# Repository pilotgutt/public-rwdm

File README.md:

# Real-Time Monitoring of Diver Status using Wireless Subsea Transmission (RWDM)

Real-Time Monitoring of Diver Status using Wireless Subsea Transmission (RWDM) is a bachelor project aimed at monitoring diver status in real time and communicating information through a wireless subsea transmission link.
This bachelor project marks the culmination of our studies in the TS3000 program at the Department of Microsystems, Faculty of Technology, Natural Sciences and Maritime Sciences. The work was carried out during the spring semester of 2026 and represents a collaborative research and development effort focused on Real-Time Wireless Diver Monitoring (RWDM).

## Repository overview

This repository contains components implemented in multiple languages:

- **C++ (56.3%)** — core/system components and performance-critical logic
- **TypeScript (17.8%)** — application/UI and supporting tooling
- **Python (15.6%)** — analysis, scripting, prototyping, or supporting services
- **C (2.3%)** — low-level/embedded or interoperability components
- **HTML (3.5%) / CSS (4.5%)** — web UI assets

## What this project is for

Typical goals for a system like this include:

- Collecting diver telemetry/status signals
- Transmitting data over a subsea wireless link
- Displaying/monitoring status in (near) real time
- Logging data for later review and analysis

## Contributing

Contributions are welcome.

Suggested workflow:

1. Fork the repo (or create a branch if you have access)
2. Make changes with clear commit messages
3. Add/update documentation and tests where applicable
4. Open a pull request with a concise description and reproduction steps (if relevant)

## License

MIT License

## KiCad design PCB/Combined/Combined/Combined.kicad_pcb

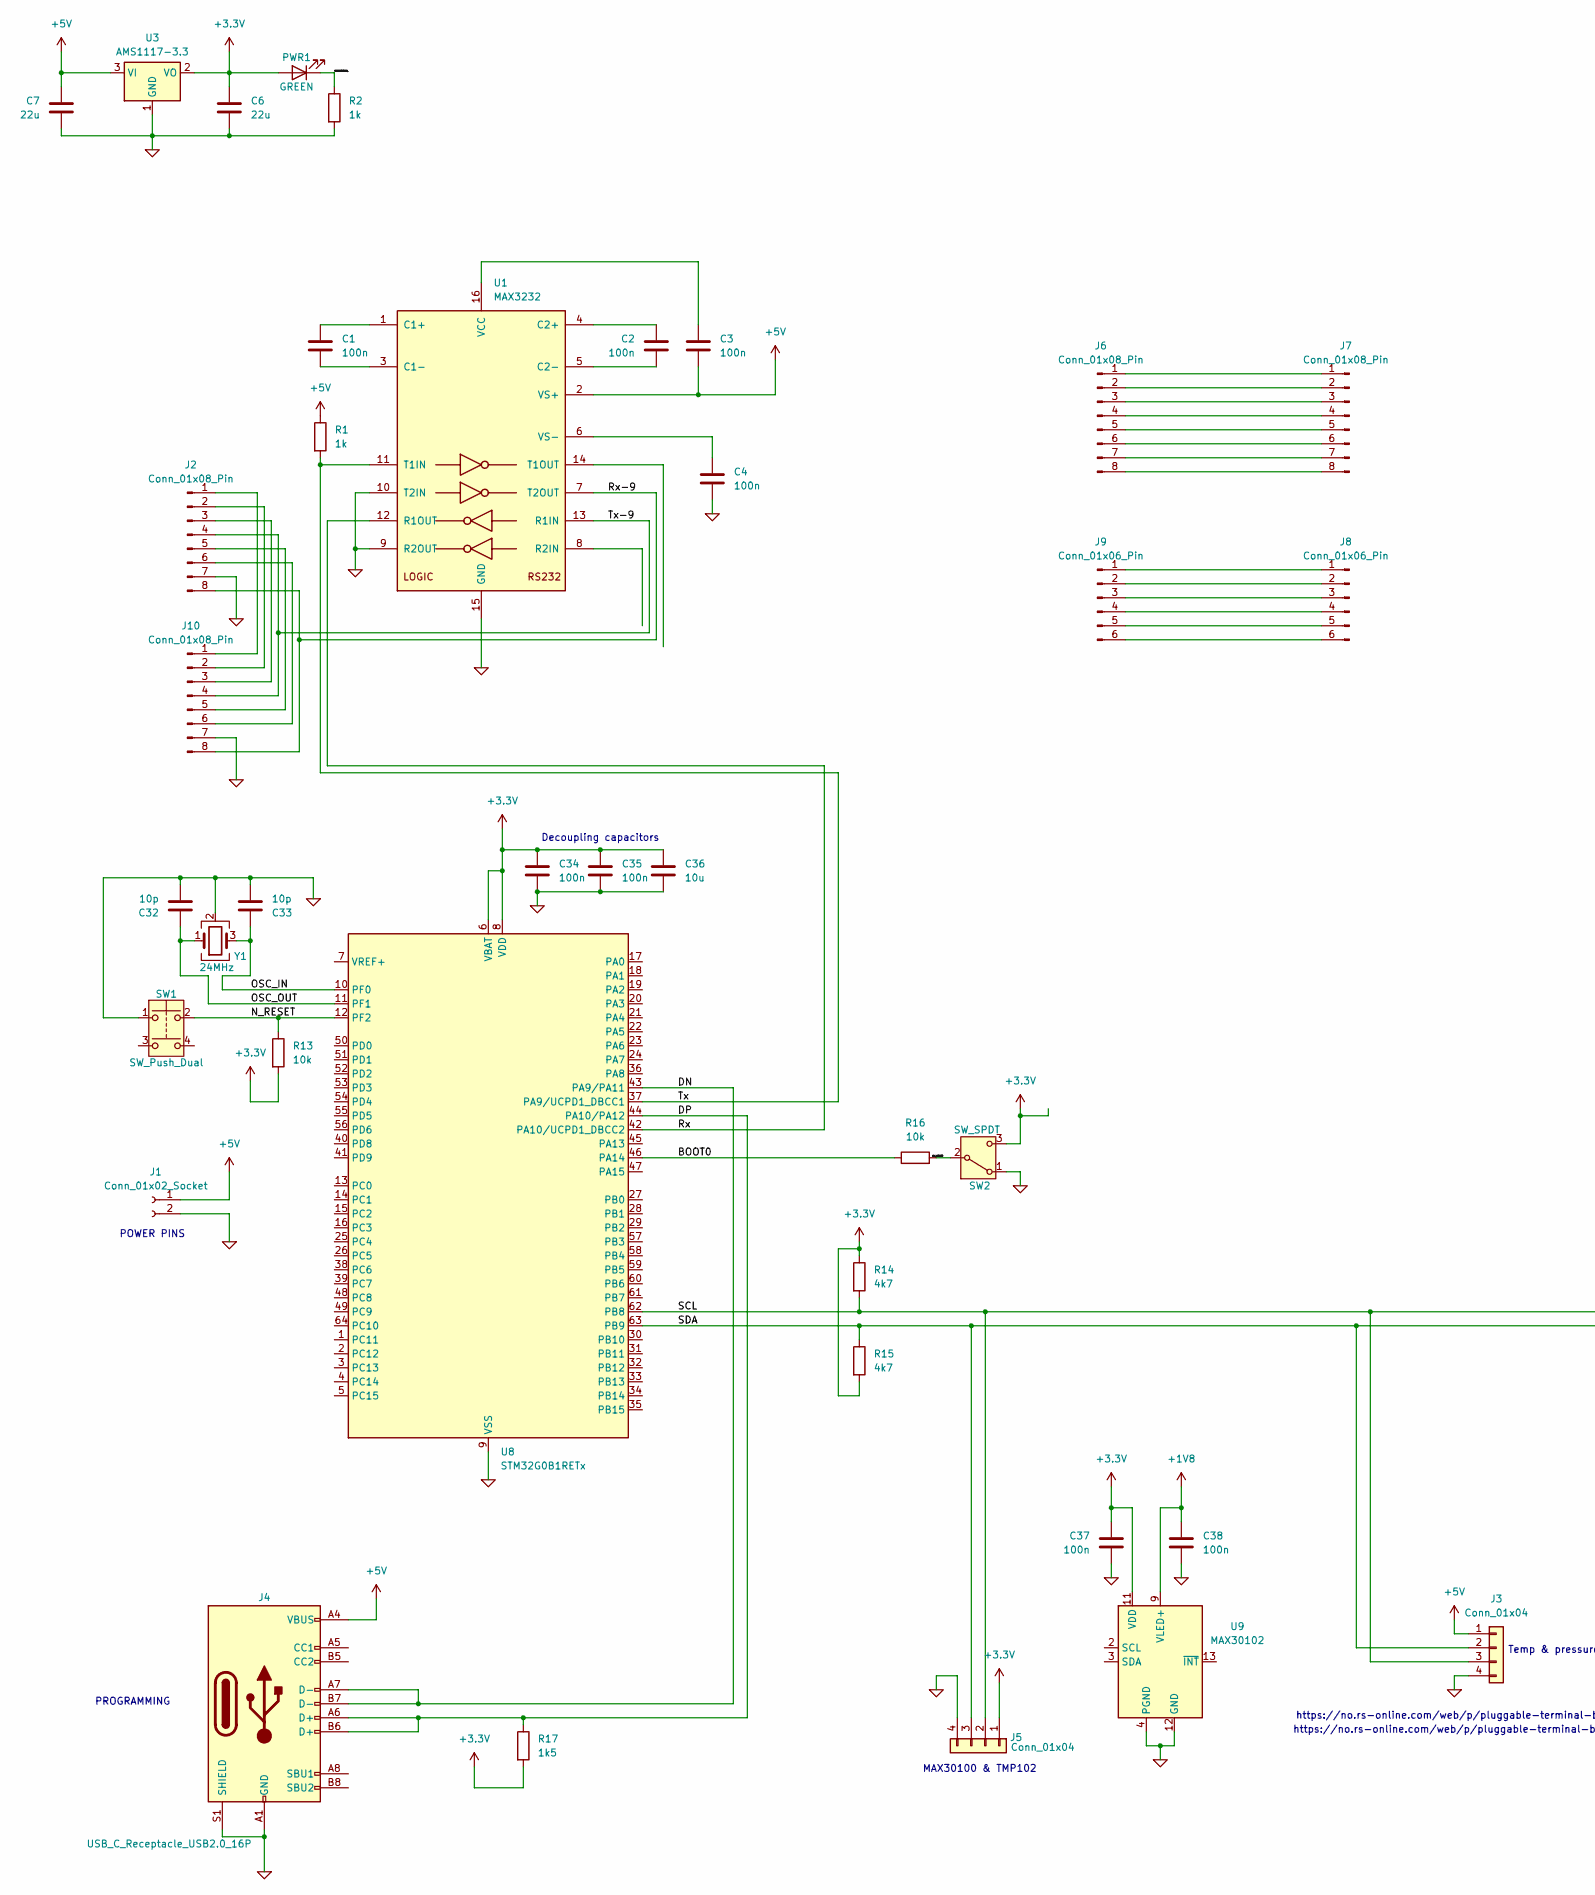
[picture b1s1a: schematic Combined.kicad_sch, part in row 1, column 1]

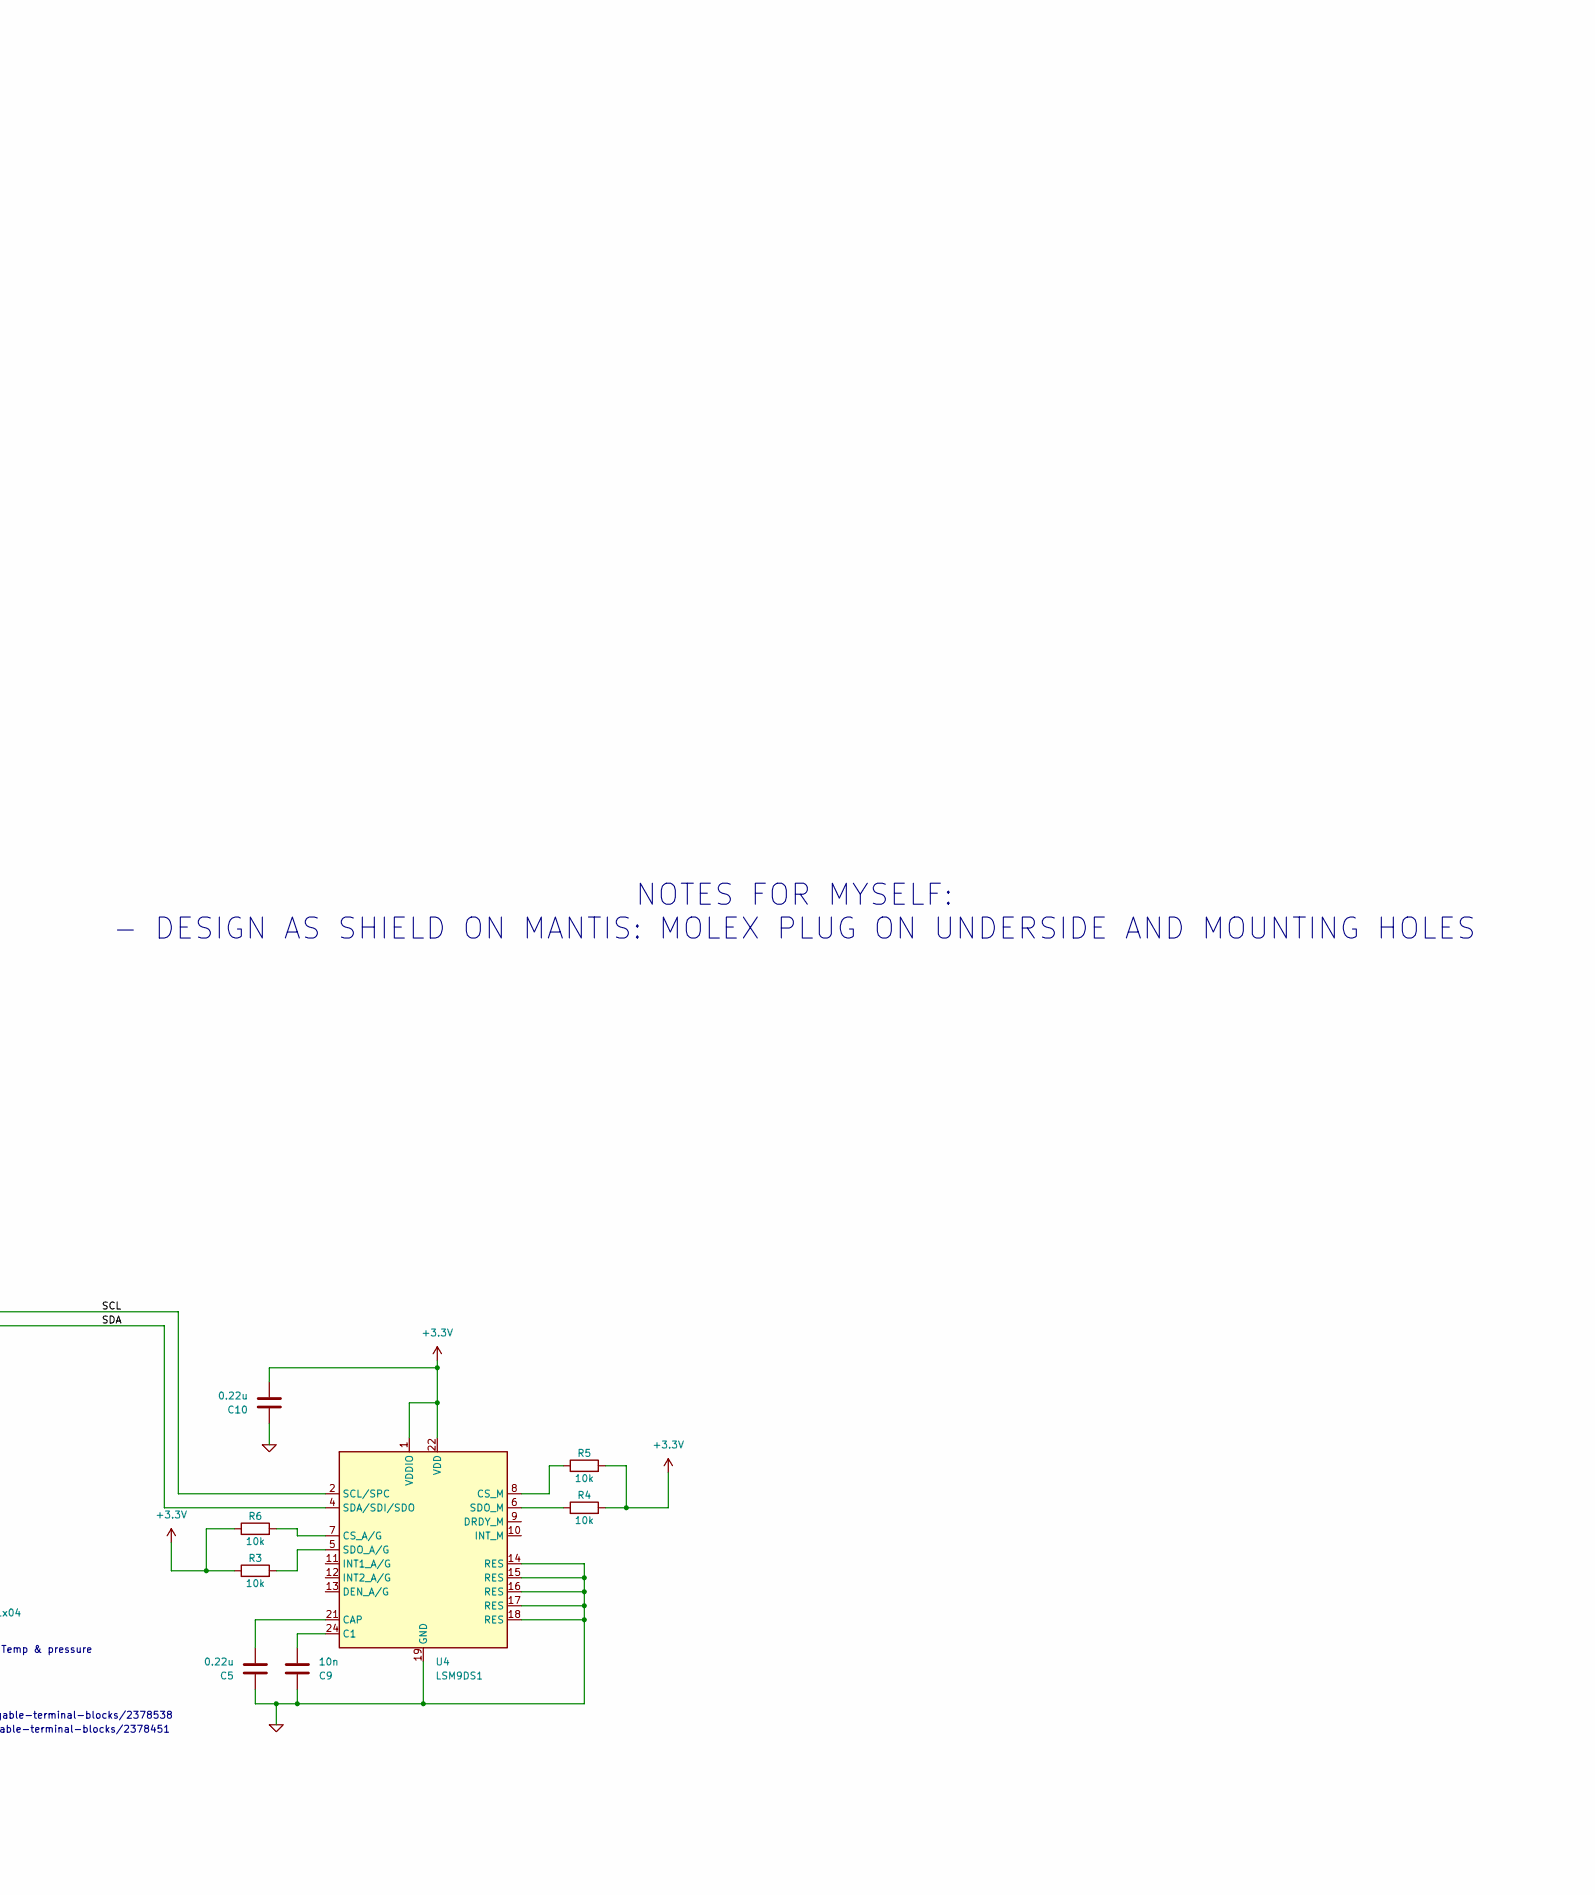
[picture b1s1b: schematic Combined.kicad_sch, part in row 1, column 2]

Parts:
C1, C2, C3, C4, C34, C35, C37, C38: 100n; C_1206_3216Metric_Pad1.33x1.80mm_HandSolder
C5, C10: 0.22u; C_1206_3216Metric_Pad1.33x1.80mm_HandSolder
C6, C7: 22u; C_1206_3216Metric_Pad1.33x1.80mm_HandSolder
C9: 10n; C_1206_3216Metric_Pad1.33x1.80mm_HandSolder
C32, C33: 10p; C_1206_3216Metric_Pad1.33x1.80mm_HandSolder
C36: 10u; C_1206_3216Metric_Pad1.33x1.80mm_HandSolder
J1: Conn_01x02_Socket; TerminalBlock_Phoenix_MKDS-1-2-3.81_1x02_P3.81mm_Horizontal
J2, J6, J7, J10: Conn_01x08_Pin; Molex_Micro-Fit_3.0_43045-0812_2x04_P3.00mm_Vertical
J3, J5: Conn_01x04; TerminalBlock_Phoenix_MKDS-1,5-4-5.08_1x04_P5.08mm_Horizont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
J4: USB_C_Receptacle_USB2.0_16P; USB_C_Receptacle_GCT_USB4105-xx-A_16P_TopMnt_Horizontal
J8, J9: Conn_01x06_Pin; Molex_Micro-Fit_3.0_43045-0612_2x03_P3.00mm_Vertical
PWR1: GREEN; LED_1206_3216Metric
R1, R2: 1k; R_1206_3216Metric_Pad1.30x1.75mm_HandSolder
R3, R4, R5, R6, R13, R16: 10k; R_1206_3216Metric_Pad1.30x1.75mm_HandSolder
R14, R15: 4k7; R_1206_3216Metric_Pad1.30x1.75mm_HandSolder
R17: 1k5; R_1206_3216Metric_Pad1.30x1.75mm_HandSolder
SW1: SW_Push_Dual; SW_Push_1P1T_NO_CK_KSC9xxG
SW2: SW_SPDT; SW_SPDT_PCM12
U1: MAX3232; SOIC-16W_7.5x10.3mm_P1.27mm
U3: AMS1117-3.3; SOT-223-3_TabPin2
U4: LSM9DS1; LGA-24L_3x3.5mm_P0.43mm
U8: STM32G0B1RETx; LQFP-64_10x10mm_P0.5mm
U9: MAX30102; Maxim_OLGA-14_3.3x5.6mm_P0.8mm
Y1: 24MHz; Crystal_SMD_3225-4Pin_3.2x2.5mm

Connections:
0: C4.2, C5.1, C6.2, C7.2, C9.1, C10.1, C32.2, C33.2, C34.2, C35.2, C36.2, C37.2, C38.2, J1.2, J2.7, J3.4, J4.A1 (GND), J4.A12 (GND), J4.B1 (GND), J4.B12 (GND), J4.S1 (SHIELD), J5.4, J10.7, R2.2, SW1.1, SW2.1 (A), U1.9 (R2OUT), U1.10 (T2IN), U1.15 (GND), U3.1 (GND), U4.14 (RES), U4.15 (RES), U4.16 (RES), U4.17 (RES), U4.18 (RES), U4.19 (GND), U4.20 (GND), U8.9 (VSS), U9.4 (PGND), U9.12 (GND), Y1.2 (G), Y1.4 (G); also elsewhere on the board
+3.3V: C6.1, C10.2, C34.1, C35.1, C36.1, C37.1, J5.1, PWR1.2 (A), R3.1, R4.2, R5.2, R6.1, R13.2, R14.1, R15.2, R17.2, SW2.3 (C), U3.2 (VO), U4.1 (VDDIO), U4.3 (VDDIO), U4.22 (VDD), U4.23 (VDD), U8.6 (VBAT), U8.8 (VDD), U9.11 (VDD)
+5V: C3.2, C7.1, J1.1, J3.1, J4.A4 (VBUS), J4.A9 (VBUS), J4.B4 (VBUS), J4.B9 (VBUS), R1.1, U1.2 (VS+), U3.3 (VI); also elsewhere on the board
/BOOT0: R16.1, U8.46 (PA14)
/DN: J4.A7 (D-), J4.B7 (D-), U8.43 (PA9/PA11)
/DP: J4.A6 (D+), J4.B6 (D+), R17.1, U8.44 (PA10/PA12)
/N_RESET: R13.1, SW1.2, U8.12 (PF2)
/OPERATIONAL: PWR1.1 (K), R2.1
/OSC_IN: C33.1, U8.10 (PF0), Y1.3
/OSC_OUT: C32.1, U8.11 (PF1), Y1.1
/Rx: U1.12 (R1OUT), U8.42 (PA10/UCPD1_DBCC2)
/Rx-9: J2.8, J10.8, U1.7 (T2OUT)
/SCL: J3.3, J5.2, R14.2, U4.2 (SCL/SPC), U8.62 (PB8)
/SDA: J3.2, J5.3, R15.1, U4.4 (SDA/SDI/SDO), U8.63 (PB9)
/SW_BOOT0: R16.2, SW2.2 (B)
/Tx: R1.2, U1.11 (T1IN), U8.37 (PA9/UCPD1_DBCC1)
/Tx-9: J2.4, J10.4, U1.13 (R1IN)
unnamed: C38.1, U9.9 (VLED+), U9.10 (VLED+)
unnamed: J6.1, J7.1
unnamed: J6.2, J7.2
unnamed: J6.3, J7.3
unnamed: J6.4, J7.4
unnamed: J6.5, J7.5
unnamed: J6.6, J7.6
unnamed: J6.7, J7.7
unnamed: J6.8, J7.8
unnamed: J8.1, J9.1
unnamed: J8.2, J9.2
unnamed: J8.3, J9.3
unnamed: J8.4, J9.4
unnamed: J8.5, J9.5
unnamed: J8.6, J9.6
unnamed: J2.1, J10.1
unnamed: J2.2, J10.2
unnamed: J2.3, J10.3
unnamed: J2.5, J10.5
unnamed: J2.6, J10.6
unnamed: C1.1, U1.1 (C1+)
unnamed: C1.2, U1.3 (C1-)
unnamed: C2.1, U1.4 (C2+)
unnamed: C2.2, U1.5 (C2-)
unnamed: C3.1, U1.16 (VCC)
unnamed: C4.1, U1.6 (VS-)
unnamed: C9.2, U4.24 (C1)
unnamed: C5.2, U4.21 (CAP)
unnamed: R6.2, U4.7 (CS_A/G)
unnamed: R5.1, U4.8 (CS_M)
unnamed: R3.2, U4.5 (SDO_A/G)
unnamed: R4.1, U4.6 (SDO_M)

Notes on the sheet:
Decoupling capacitors
PROGRAMMING
https://no.rs-online.com/web/p/pluggable-terminal-blocks/2378538
NOTES FOR MYSELF: - DESIGN AS SHIELD ON MANTIS: MOLEX PLUG ON UNDERSIDE AND MOUNTING HOLES
MAX30100 & TMP102
https://no.rs-online.com/web/p/pluggable-terminal-blocks/2378451
Temp & pressure
POWER PINS

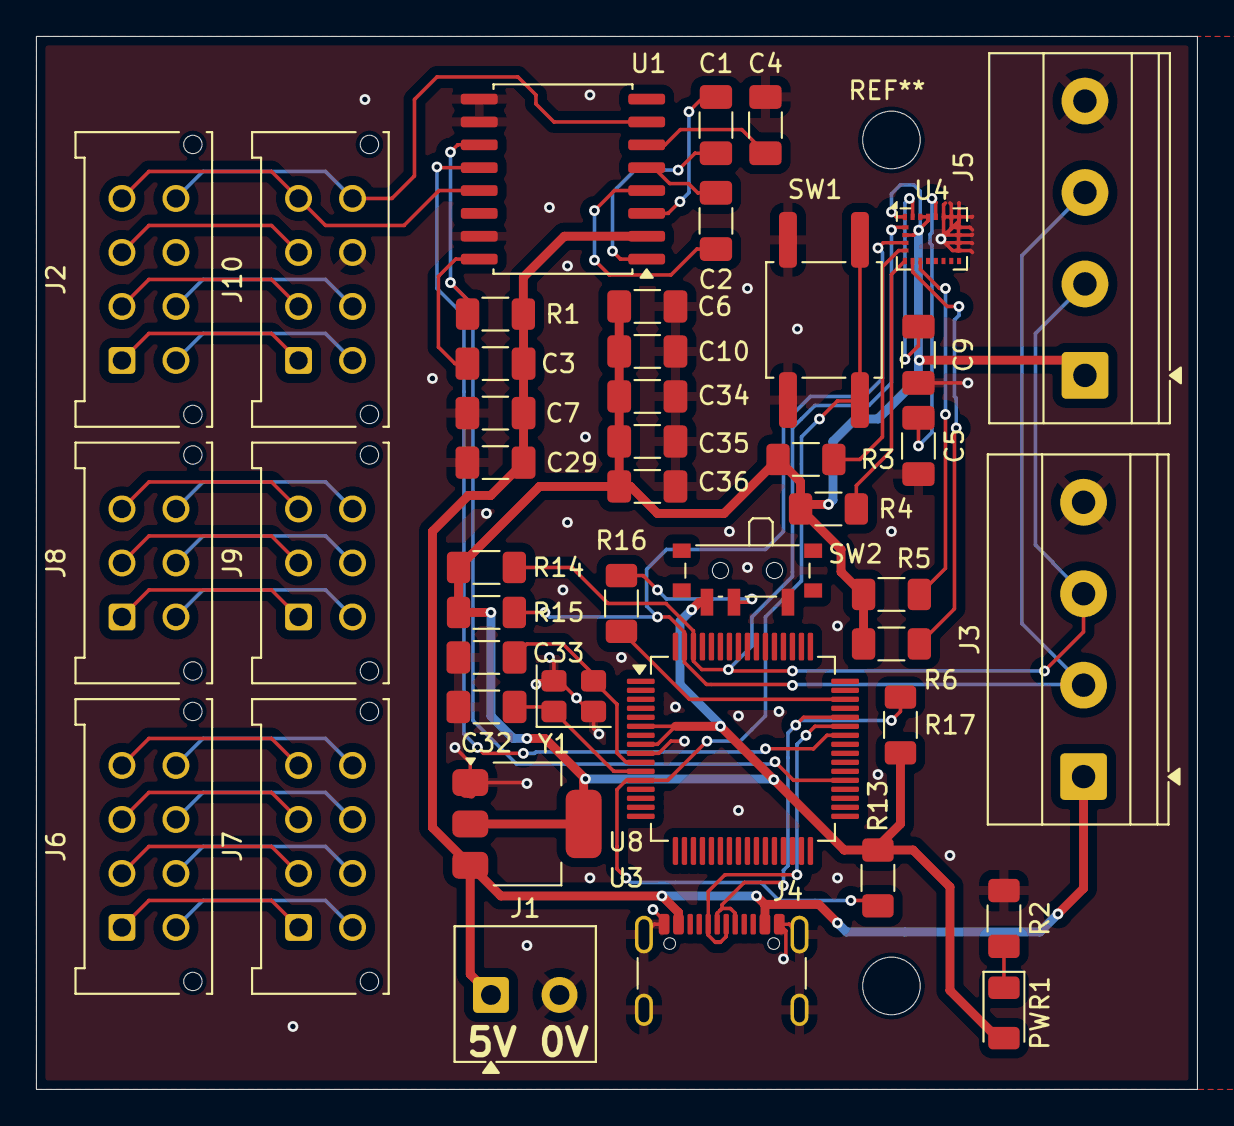
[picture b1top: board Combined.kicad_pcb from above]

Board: 2 copper layers, 64.5 x 58.5 mm, 44 parts (0 on the bottom side), 48 nets.

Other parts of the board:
C29: 22u; C_1206_3216Metric_Pad1.33x1.80mm_HandSolder

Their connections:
0: C29.2; also elsewhere on the board
+5V: C29.1; also elsewhere on the board

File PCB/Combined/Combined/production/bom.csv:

Designator,Footprint,Quantity,Value,LCSC Part #
"C1, C2, C3, C34, C35, C4",1206,6,100n,
"C10, C5",1206,2,0.22u,
"C29, C6, C7",1206,3,22u,
"C32, C33",1206,2,10p,
C36,1206,1,10u,
C9,1206,1,10n,
J1,TerminalBlock_Phoenix_MKDS-1-2-3.81_1x02_P3.81mm_Horizontal,1,Conn_01x02_Socket,
"J10, J2, J6, J7",Molex_Micro-Fit_3.0_43045-0812_2x04_P3.00mm_Vertical,4,Conn_01x08_Pin,
"J3, J5","TerminalBlock_Phoenix_MKDS-1,5-4-5.08_1x04_P5.08mm_Horizontal",2,Conn_01x04,
J4,USB_C_Receptacle_GCT_USB4105-xx-A_16P_TopMnt_Horizontal,1,USB_C_Receptacle_USB2.0_16P,
"J8, J9",Molex_Micro-Fit_3.0_43045-0612_2x03_P3.00mm_Vertical,2,Conn_01x06_Pin,
PWR1,1206,1,GREEN,
"R1, R2",1206,2,1k,
"R13, R16, R3, R4, R5, R6",1206,6,10k,
"R14, R15",1206,2,4k7,
R17,1206,1,1k5,
SW1,SW_Push_1P1T_NO_CK_KSC9xxG,1,SW_Push_Dual,
SW2,SW_SPDT_PCM12,1,SW_SPDT,
U1,SOIC-16W_7.5x10.3mm_P1.27mm,1,MAX3232,
U3,SOT-223-3_TabPin2,1,AMS1117-3.3,
U4,LGA-24L_3x3.5mm_P0.43mm,1,LSM9DS1,
U8,LQFP-64_10x10mm_P0.5mm,1,STM32G0B1RETx,
Y1,Crystal_SMD_3225-4Pin_3.2x2.5mm,1,24MHz,

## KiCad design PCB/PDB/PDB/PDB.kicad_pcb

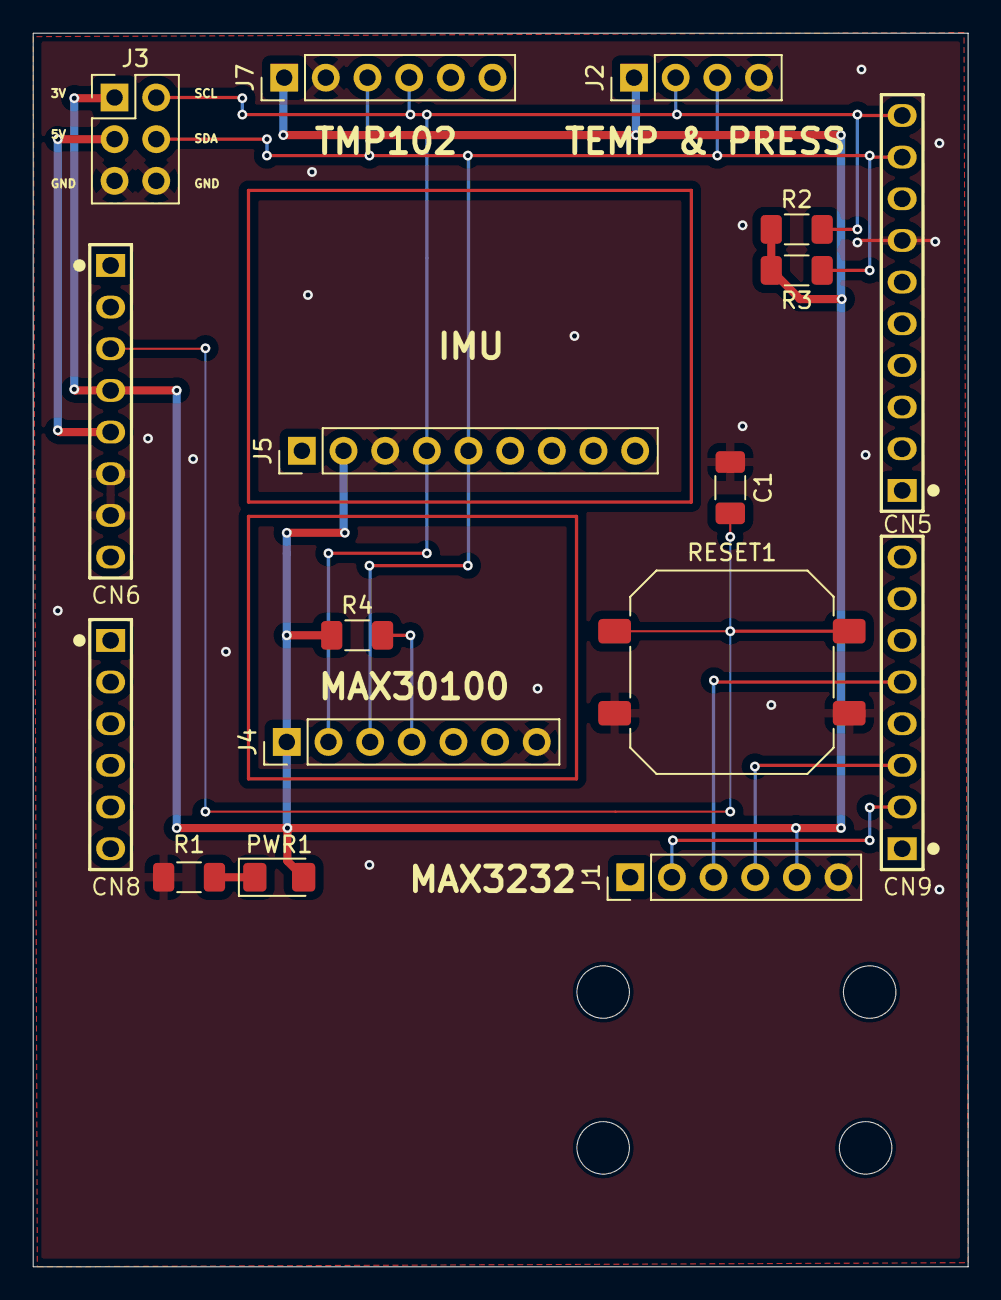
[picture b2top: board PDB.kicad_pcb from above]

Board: 2 copper layers, 57.0 x 75.2 mm, 17 parts (0 on the bottom side), 11 nets.

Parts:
C1: 100n; C_1206_3216Metric_Pad1.33x1.80mm_HandSolder
CN5: Header 10X1_Female; 1*10P_FEMALE
CN6, CN9: Header 8X1_Female; 1*8P_FEMALE
CN8: Header 6X1_Female; 1*6P_FEMALE
J1, J7: Conn_01x06_Socket; PinHeader_1x06_P2.54mm_Vertical
J2: Conn_01x04_Socket; PinHeader_1x04_P2.54mm_Vertical
J3: Conn_01x06_Pin; PinHeader_2x03_P2.54mm_Vertical
J4: Conn_01x07_Socket; PinHeader_1x07_P2.54mm_Vertical
J5: Conn_01x09_Socket; PinHeader_1x09_P2.54mm_Vertical
PWR1: GREEN; D_1206_3216Metric_Pad1.42x1.75mm_HandSolder
R1: 120; R_1206_3216Metric_Pad1.30x1.75mm_HandSolder
R2, R3, R4: 4k7; R_1206_3216Metric_Pad1.30x1.75mm_HandSolder
RESET1: SW_Push_Dual; SW_Push_1P1T_NO_CK_PTS125Sx43SMTR

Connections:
0: C1.2, CN5.7, CN6.6, CN6.7, J1.6, J2.4, J3.5, J3.6, J4.7, J5.3, J7.2, R1.2, RESET1.2
+3V3: CN6.4, J1.5, J2.1, J3.1, J4.1, J5.2, J7.1, PWR1.2 (A), R2.1, R3.2, R4.1
+5V: CN6.5, J3.3
/CTS: CN9.5, J1.3
/NRST: C1.1, CN6.3, RESET1.1
/RTS: CN9.3, J1.4
/SCL: CN5.10, J2.2, J3.2, J4.2, J5.4, J7.4, R2.2
/SDA: CN5.9, J2.3, J3.4, J4.3, J5.5, J7.3, R3.1
/Tx: CN9.2, J1.2
unnamed: J4.4, R4.2
unnamed: PWR1.1 (K), R1.1

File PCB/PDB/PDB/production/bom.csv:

Designator,Footprint,Quantity,Value,LCSC Part #
C1,1206,1,100n,
CN5,1*10P_FEMALE,1,Header 10X1_Female,
"CN6, CN9",1*8P_FEMALE,2,Header 8X1_Female,
CN8,1*6P_FEMALE,1,Header 6X1_Female,
"J1, J7",PinHeader_1x06_P2.54mm_Vertical,2,Conn_01x06_Socket,
J2,PinHeader_1x04_P2.54mm_Vertical,1,Conn_01x04_Socket,
J3,PinHeader_2x03_P2.54mm_Vertical,1,Conn_01x06_Pin,
J4,PinHeader_1x07_P2.54mm_Vertical,1,Conn_01x07_Socket,
J5,PinHeader_1x09_P2.54mm_Vertical,1,Conn_01x09_Socket,
PWR1,1206,1,GREEN,
R1,1206,1,120,
"R2, R3, R4",1206,3,4k7,
RESET1,SW_Push_1P1T_NO_CK_PTS125Sx43SMTR,1,SW_Push_Dual,

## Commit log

2026-04-30 Initial commit
    Making private bachelor repo files public in a new repo.
2026-04-30 Initialize README with project details and guidelines
    Added project overview, goals, contributing guidelines, and license information to README.
2026-04-30 for my eyes only...
    Delete gstreamer_node/PIPELINE_DOCUMENTATION.md
2026-04-30 Added CAD drawings for auto adjuster
    Added CAD drawings for auto adjuster
2026-04-30 Added underwater bluetooth data and plot program
2026-04-30 Add usage instructions to readme.md
    Added instructions for using the auto adjuster robot system based on signal strength and diver's position.
2026-04-30 Clarify COM port change instruction in readme
    Updated readme to emphasize changing the COM port in the code.
2026-04-30 Update warning message format in readme
2026-04-30 Change warning note to reminder in readme
    Updated warning note to a reminder in readme.
2026-04-30 Fix typo in readme regarding COM port
2026-04-30 Update readme with Decawave nodes and drift notes
    Added notes about Decawave positioning nodes and testing observations.
